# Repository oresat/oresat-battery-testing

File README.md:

# oresat-battery-testing

Battery testing software and circuitry for testing cells and batteries to fly on the ISS

General Project Documentation aimed at newcomers:
https://docs.google.com/document/d/1XBeL89PfLqN40TnOpgzCtq_2dRlRgkeDnu8u4CYXgOA/edit

V1.0 of the PCB layout:

### Software
### Setup
- Clone oresat-battery-testing.
- Install dependencies: `$ sudo apt install libusb-1.0-0-dev pkg-config python3-dev`
- Install pyusb: "pip install pyusb" or if that doesn't work, use "pip install pyusb --break-system-packages"
- Build Python extension for libb6: `$ make -C libraries`

### More Dependencies
To get u6 to work (import u6) you must install the labjack-ljm python library which is different from the labjack-ljm package

sudo pip install labjack-ljm --break-system-packages 
The above line installed labjack-ljm

You need to install Exodriver in order for u6 to work

git clone https://github.com/labjack/exodriver.git
cd exodriver
sudo ./install.sh

You will also need LabJackPython:
sudo pip install LabJackPython --break-system-packages

### Udev Setup
Copy the .rules files (from the Battery Tester folder) into the folder on your computer which contains rules files for udev.

For example on an Ubuntu system: /etc/udev/rules.d

This will allow you to run [filename].py without requiring sudo.

Note that you will have to find the correct devpaths again if you use your own device, then modify 99-b6mini.rules accordingly.

Choose a USB port on your computer to plug the battery board into and do not change it.

### Run
cd battery_tester
python battery_test_jig.py
or better yet: python testing_bay.py

If you get an import error about libb6:
...run the Makefile in battery_tester/libb6 to make an object file.

### Battery Cells
In each bank are four battery slots. The battery slot on each bank that is closest to the LabJack is slot D, then up from there is C, B, and A. Each battery slot corresponds to the charger of the same designation. If Battery A (on whichever battery bank currently selected) is not charging, something may be wrong with Charger A, for instance.

### Battery_Tester Design
__chargers_backend.py__
In the battery chargers section, does not deal with labjack at all.
Jobs:
- A) Hold the data required for charging batteries: ChargeProfile, Charger Serial Paths
- B) Hold the functions required for charging batteries: start_charging(), stop_charging(), define_charger_serial_paths()

__labjack_backend.py__
In the labjack battery data-getting section, does not interact with chargers at all.
Jobs:
- A) Hold data required for labjack commands: PINS,
	- i. Have notes about each of the functions (or at least a mention) of the functions we're using such as getAIN()
- B) Hold dataclass for collecting temperature and voltage data: class BankData
- C) Hold calculation/conversion functions for getting temps and volts: get_actual_temp(), get_data()
- D) A general STOP() function for the labjack

__scribe_backend.py__
In the labjack battery data-getting section, does not interact with anything.
Jobs:
- A) Hold functions for writing to csv file, including timestamps.

__main.py__ (or something similar)
This is the general frontend that combines all parts and holds a class with functions to charge, discharge, test, etc.
- A) Select a battery bank/battery and do any or all of the following:
	- i. Charge.
	- ii. Discharge.
	- iii. Get voltage and temperature. Write to csv with timestamp.

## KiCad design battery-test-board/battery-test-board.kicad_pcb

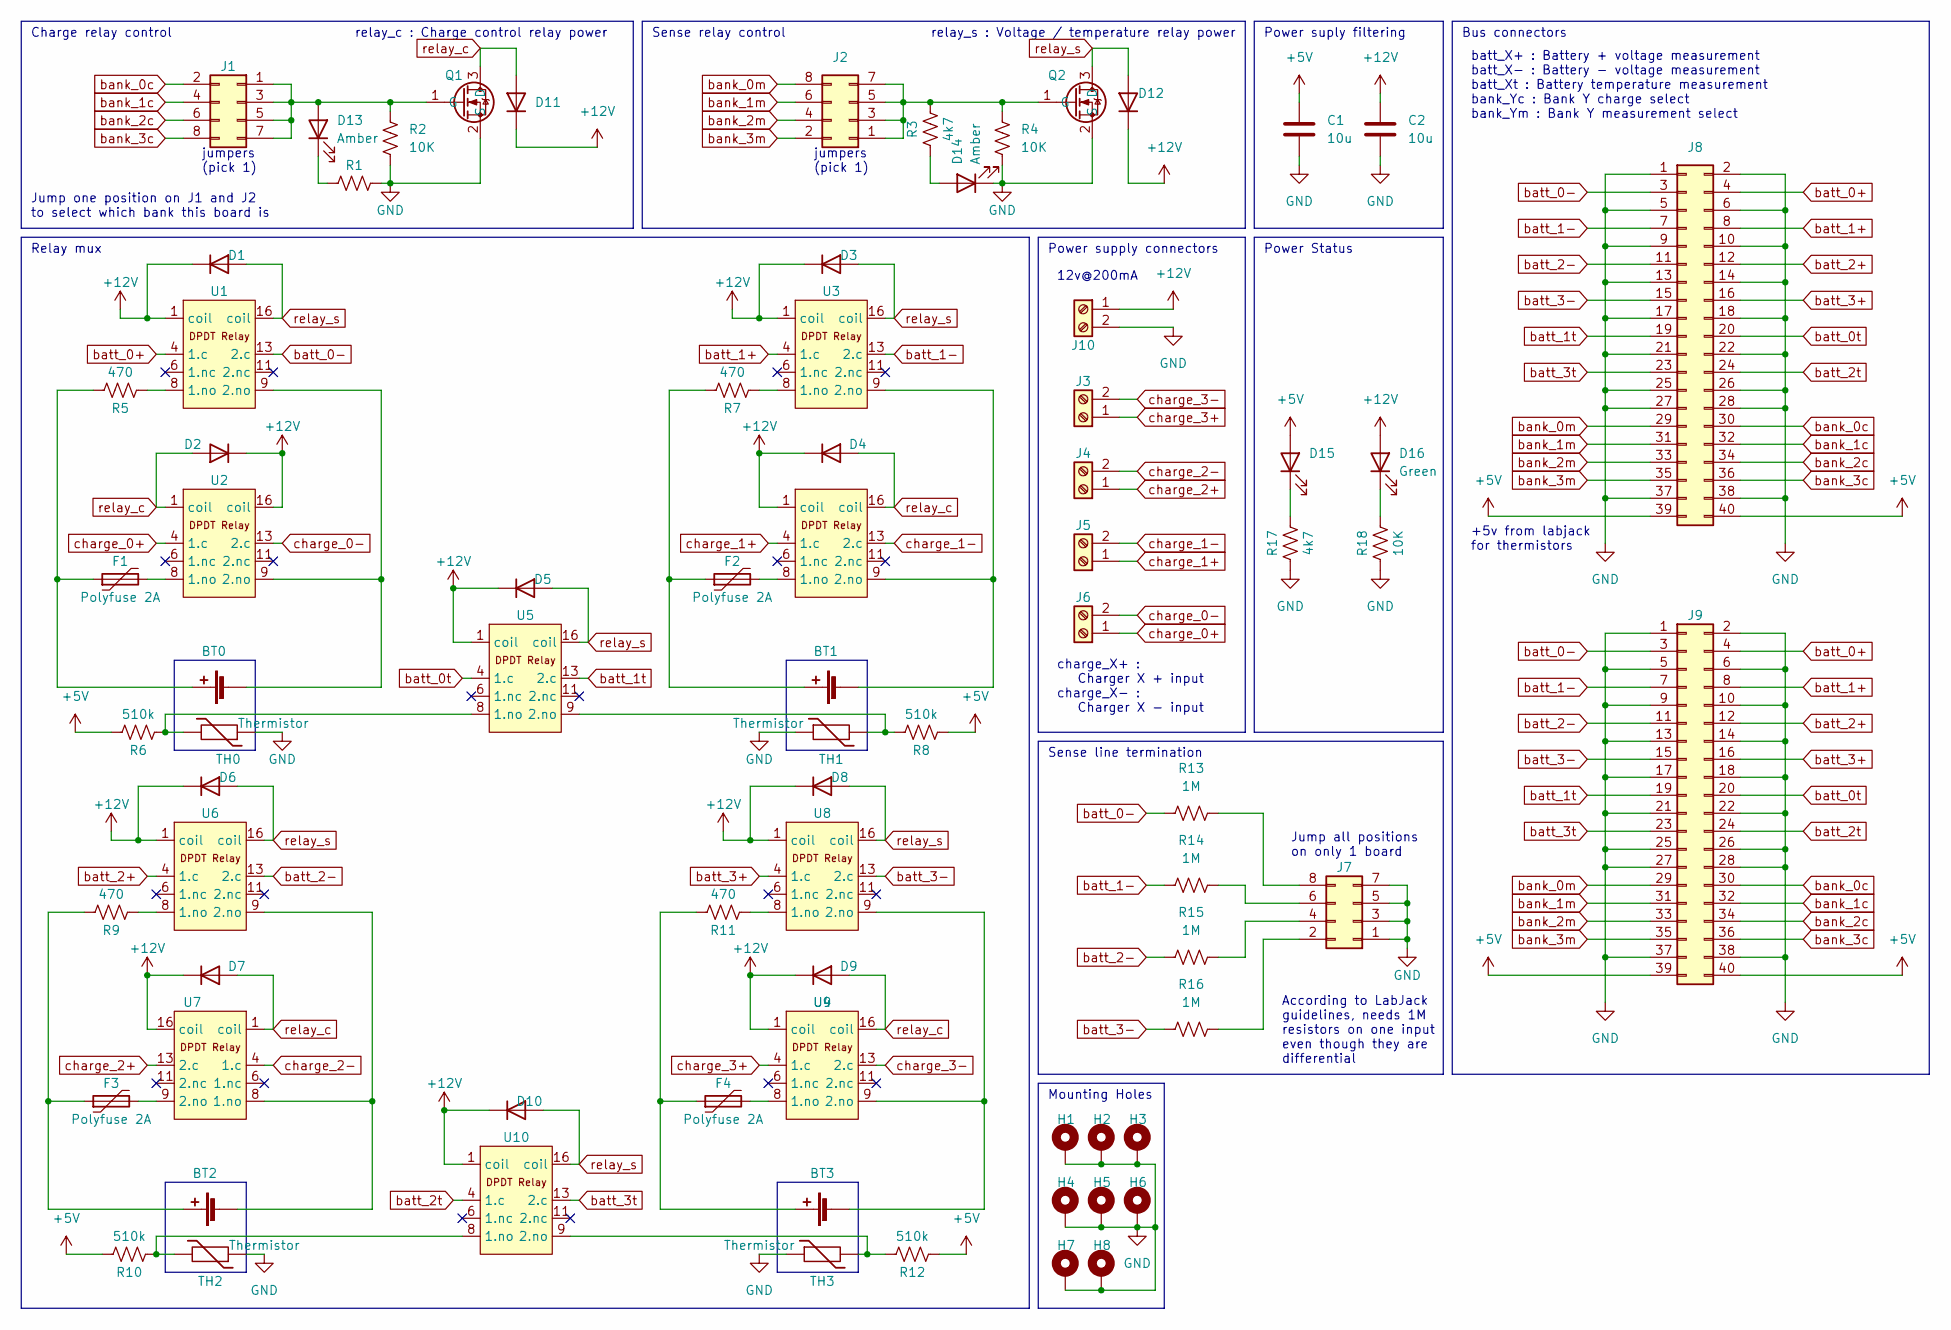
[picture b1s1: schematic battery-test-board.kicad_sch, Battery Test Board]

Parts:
BT0, BT1, BT2, BT3: battery; BatteryHolder_MPD_BH-18650-PC2; MPN BK-18650-PC2
C1, C2: 10u; C_1206_3216Metric; MPN CL31A106KAHNNNE
D1, D2, D3, D4, D5, D6, D7, D8, D9, D10, D11, D12: diode; D_0805_2012Metric; MPN NSR05T40P2T5G
D13, D14: Amber; LED_1206_3216Metric; MPN 150120AS75000
D15: MPN 150120VS75000
D16: Green; LED_1206_3216Metric; MPN 150120VS75000
F1, F2, F3, F4: Polyfuse 2A; Fuse_2920_7451Metric; MPN 2920L100PR
H1, H2, H3, H4, H5, H6, H7, H8: MountingHole_Pad; MountingHole_3.2mm_M3_Pad_Via
J1, J2, J7: Conn_02x04_Odd_Even; PinSocket_2x04_P2.54mm_Vertical; MPN PR20204VBDN
J3, J4, J5, J6, J10: Screw_Terminal_01x02; TerminalBlock_Altech_AK300-2_P5.00mm; MPN EBAA-02-C
J8, J9: connector; IDC-Header_2x20_P2.54mm_Vertical; MPN 732-5401-ND
Q1, Q2: mosfet; SOT-23; MPN PJA3412-AU_R1_000A1
R1: MPN RMCF1206FT4K70
R2, R4, R18: 10K; R_1206_3216Metric; MPN RMCF1206FT10K0
R3, R17: 4k7; R_1206_3216Metric; MPN RMCF1206FT4K70
R5, R7, R9, R11: 470; R_1206_3216Metric; MPN RMCF1206FT470R
R6, R8, R10, R12: 510k; R_1206_3216Metric; MPN RMCF1206FT510K
R13, R14, R15, R16: 1M; R_1206_3216Metric; MPN RMCF1206FT1M00
TH0, TH1, TH2, TH3: Thermistor; thermister-solderin; MPN NXFT15XH103FA1B025
U1, U2, U3, U4, U5, U6, U7, U8, U9, U10: relay; relay-dpdt-.3in; MPN J104D2C12VDC.15S‎

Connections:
+5V: C1.1, D15.2 (A), J8.39, J8.40, J9.39, J9.40, R6.1, R8.2, R10.1, R12.2
+12V: C2.1, D1.1 (K), D2.1 (K), D3.1 (K), D4.1 (K), D5.1 (K), D6.1 (K), D7.1 (K), D8.1 (K), D9.1 (K), D10.1 (K), D11.1 (K), D12.1 (K), D16.2 (A), J10.1, U1.1 (coil), U2.16 (coil), U3.1 (coil), U4.1 (coil), U5.1 (coil), U6.1 (coil), U7.16 (coil), U8.1 (coil), U9.1 (coil), U10.1 (coil)
GND: C1.2, C2.2, D14.1 (K), H1.1, H2.1, H3.1, H4.1, H5.1, H6.1, H7.1, H8.1, J7.1, J7.3, J7.5, J7.7, J8.1, J8.2, J8.5, J8.6, J8.9, J8.10, J8.13, J8.14, J8.17, J8.18, J8.21, J8.22, J8.25, J8.26, J8.27, J8.28, J8.37, J8.38, J9.1, J9.2, J9.5, J9.6, J9.9, J9.10, J9.13, J9.14, J9.17, J9.18, J9.21, J9.22, J9.25, J9.26, J9.27, J9.28, J9.37, J9.38, J10.2, Q1.2 (S), Q2.2 (S), R1.1, R2.2, R4.2, R17.2, R18.2, TH0.1, TH1.1, TH2.1, TH3.1
unnamed: BT0.1 (+), F1.1, R5.1
unnamed: BT0.2 (-), U1.9 (2.no), U2.9 (2.no)
unnamed: BT1.1 (+), F2.1, R7.1
unnamed: BT1.2 (-), U3.9 (2.no), U4.9 (2.no)
unnamed: BT2.1 (+), F3.1, R9.1
unnamed: BT2.2 (-), U6.9 (2.no), U7.8 (1.no)
unnamed: BT3.1 (+), F4.1, R11.1
unnamed: BT3.2 (-), U8.9 (2.no), U9.9 (2.no)
unnamed: D13.1 (K), R1.2
unnamed: D13.2 (A), J1.1, J1.3, J1.5, J1.7, Q1.1 (G), R2.1
unnamed: D14.2 (A), R3.2
unnamed: D15.1 (K), R17.1
unnamed: D16.1 (K), R18.1
unnamed: F1.2, U2.8 (1.no)
unnamed: F2.2, U4.8 (1.no)
unnamed: F3.2, U7.9 (2.no)
unnamed: F4.2, U9.8 (1.no)
unnamed: J2.1, J2.3, J2.5, J2.7, Q2.1 (G), R3.1, R4.1
unnamed: J7.2, R16.1
unnamed: J7.4, R15.2
unnamed: J7.6, R14.2
unnamed: J7.8, R13.2
unnamed: R5.2, U1.8 (1.no)
unnamed: R6.2, TH0.2, U5.8 (1.no)
unnamed: R7.2, U3.8 (1.no)
unnamed: R8.1, TH1.2, U5.9 (2.no)
unnamed: R9.2, U6.8 (1.no)
unnamed: R10.2, TH2.2, U10.8 (1.no)
unnamed: R11.2, U8.8 (1.no)
unnamed: R12.1, TH3.2, U10.9 (2.no)
bank_0c: J1.2, J8.30, J9.30
bank_0m: J2.8, J8.29, J9.29
bank_1c: J1.4, J8.32, J9.32
bank_1m: J2.6, J8.31, J9.31
bank_2c: J1.6, J8.34, J9.34
bank_2m: J2.4, J8.33, J9.33
bank_3c: J1.8, J8.36, J9.36
bank_3m: J2.2, J8.35, J9.35
batt_0+: J8.4, J9.4, U1.4 (1.c)
batt_0-: J8.3, J9.3, R13.1, U1.13 (2.c)
batt_0t: J8.20, J9.20, U5.4 (1.c)
batt_1+: J8.8, J9.8, U3.4 (1.c)
batt_1-: J8.7, J9.7, R14.1, U3.13 (2.c)
batt_1t: J8.19, J9.19, U5.13 (2.c)
batt_2+: J8.12, J9.12, U6.4 (1.c)
batt_2-: J8.11, J9.11, R15.1, U6.13 (2.c)
batt_2t: J8.24, J9.24, U10.4 (1.c)
batt_3+: J8.16, J9.16, U8.4 (1.c)
batt_3-: J8.15, J9.15, R16.2, U8.13 (2.c)
batt_3t: J8.23, J9.23, U10.13 (2.c)
charge_0+: J6.1, U2.4 (1.c)
charge_0-: J6.2, U2.13 (2.c)
charge_1+: J5.1, U4.4 (1.c)
charge_1-: J5.2, U4.13 (2.c)
charge_2+: J4.1, U7.13 (2.c)
charge_2-: J4.2, U7.4 (1.c)
charge_3+: J3.1, U9.4 (1.c)
charge_3-: J3.2, U9.13 (2.c)
relay_c: D2.2 (A), D4.2 (A), D7.2 (A), D9.2 (A), D11.2 (A), Q1.3 (D), U2.1 (coil), U4.16 (coil), U7.1 (coil), U9.16 (coil)
relay_s: D1.2 (A), D3.2 (A), D5.2 (A), D6.2 (A), D8.2 (A), D10.2 (A), D12.2 (A), Q2.3 (D), U1.16 (coil), U3.16 (coil), U5.16 (coil), U6.16 (coil), U8.16 (coil), U10.16 (coil)

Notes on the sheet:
jumpers (pick 1)
Jump one position on J1 and J2 to select which bank this board is
Jump all positions on only 1 board
Mounting Holes
Sense line termination
relay_c : Charge control relay power
Power Status
Sense relay control
Power supply connectors
relay_s : Voltage / temperature relay power
12v@200mA
+5v from labjack for thermistors
Power suply filtering
charge_X+ : Charger X + input charge_X- : Charger X - input
batt_X+ : Battery + voltage measurement batt_X- : Battery - voltage measurement batt_Xt : Battery temperature measurement bank_Yc : Bank Y charge select bank_Ym : Bank Y measurement select
According to LabJack guidelines, needs 1M resistors on one input even though they are differential
Relay mux
Bus connectors
Charge relay control

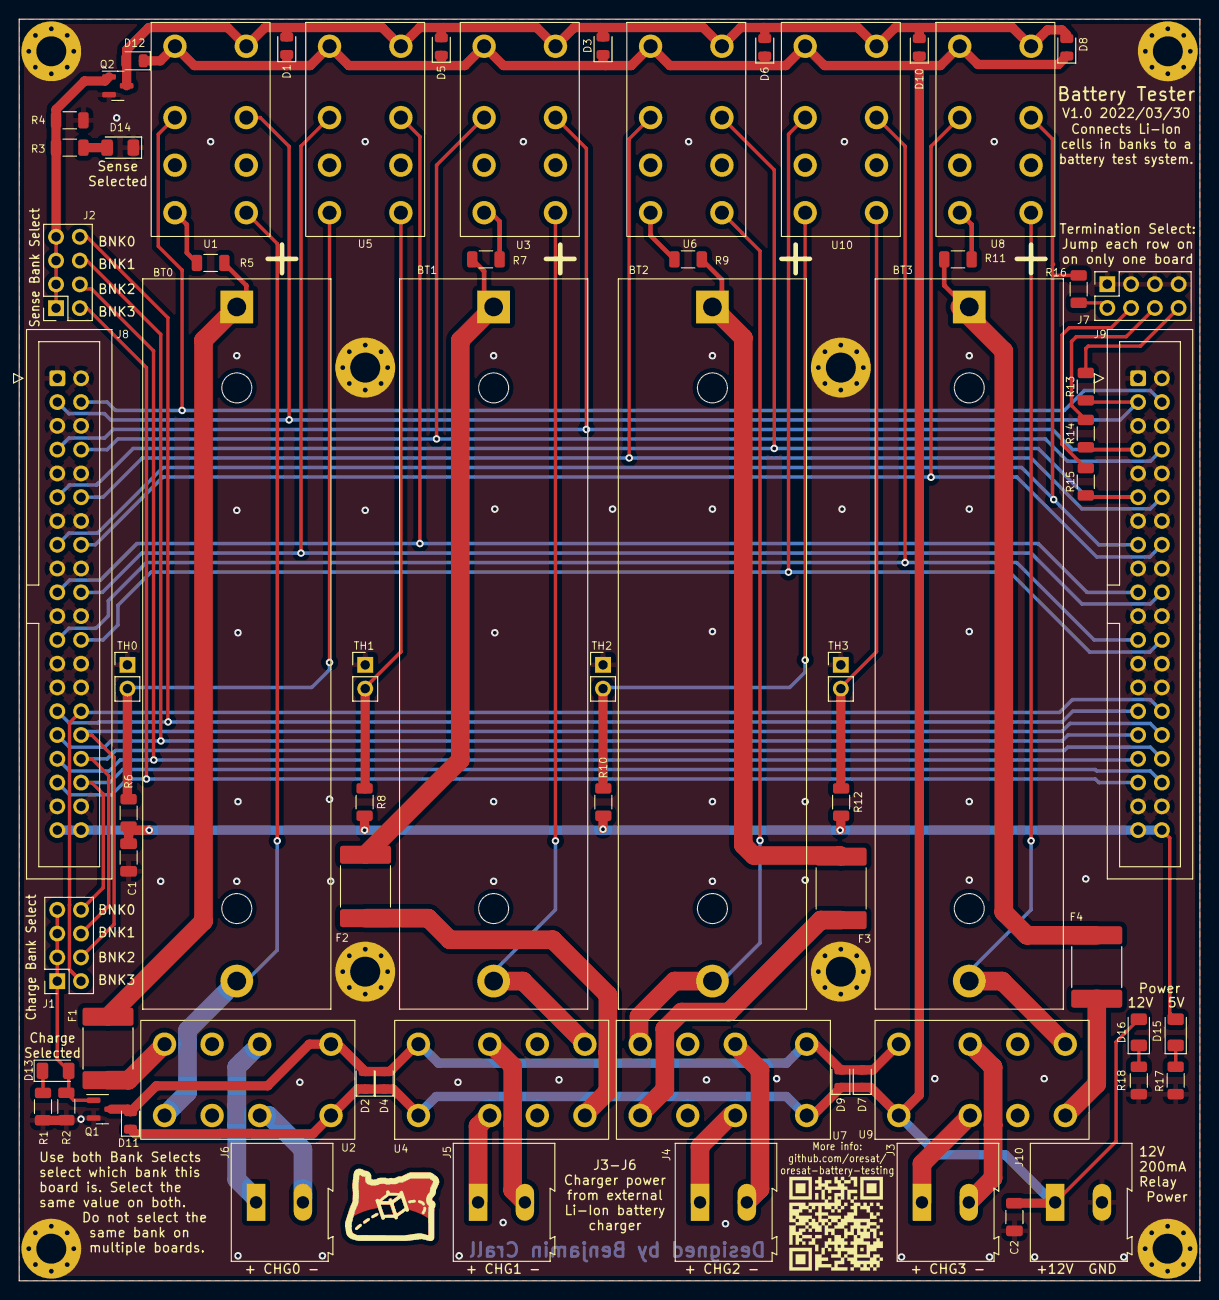
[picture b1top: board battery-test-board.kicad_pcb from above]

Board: 2 copper layers, 126.1 x 134.7 mm, 78 parts (0 on the bottom side), 63 nets.

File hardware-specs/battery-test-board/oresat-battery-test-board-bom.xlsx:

OreSat Battery Test Board v1
Qty | Parts | MFR | MPN | Description | Assembly | STOCK | DIST | DPN | DIST2 | DPN2
4 | BT0, BT1, BT2, BT3 | MPD (Memory Protection Devices) | BK-18650-PC2 | Battery Holder (Open) 18650 1 Cell PC Pin | TH |  | Digikey | BK-18650-PC2-ND
2 | C1, C2 | Samsung Electro-Mechanics | CL31A106KAHNNNE | 10 µF ±10% 25V Ceramic Capacitor X5R 1206 (3216 Metric) | SMD |  | Digikey | 1276-1075-1-ND
12 | D1, D2, D3, D4, D5, D6, D7, D8, D9, D10, D11, D12 | onsemi | NSR05T40P2T5G | Diode Schottky 40 V 500mA (DC) Surface Mount SOD-923 | SMD |  | Digikey | NSR05T40P2T5GOSCT-ND
2 | D13, D14 | Würth Elektronik | 150120AS75000 | Amber 605nm LED Indication - Discrete 2V 1206 (3216 Metric) | SMD |  | Digikey | 732-4988-1-ND
2 | D15, D16 | Würth Elektronik | 150120VS75000 | Green 570nm LED Indication - Discrete 2V 1206 (3216 Metric) | SMD |  | Digikey | 732-4993-1-ND
4 | F1, F2, F3, F4 | Littelfuse Inc. | 2920L100PR | Polymeric PTC Resettable Fuse 33V 1.1 A Ih Surface Mount 2920 (7351 Metric), Co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 | SMD |  | Digikey | F2868CT-ND
3 | J1, J2, J7 | METZ CONNECT USA Inc. | PR20204VBDN | Connector Header Through Hole 8 position 0.100" (2.54mm) | TH |  | Digikey | 1849-PR20204VBDN-ND
5 | J3, J4, J5, J6, J10 | Adam Tech | EBAA-02-C | 2 Position Wire to Board Terminal Block Horizontal with Board 0.197" (5.00mm) T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 | TH |  | Digikey | 2057-EBAA-02-C-ND
2 | J8, J9 | Würth Elektronik | 732-5401-ND | Connector Header Through Hole 40 position 0.100" (2.54mm) | TH |  | Digikey | 732-5401-ND
2 | Q1, Q2 | Panjit International Inc. | PJA3412-AU_R1_000A1 | N-Channel 20 V 4.1A (Ta) 1.25W (Ta) Surface Mount SOT-23k | SMD |  | Digikey | 3757-PJA3412-AU_R1_000A1CT-ND
3 | R1, R3, R17 | Stackpole Electronics Inc | RMCF1206FT4K70 | 4.7 kOhms ±1% 0.25W, 1/4W Chip Resistor 1206 (3216 Metric) Automotive AEC-Q200 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 | SMD |  | Digikey | RMCF1206FT4K70CT-ND
3 | R2, R4, R18 | Stackpole Electronics Inc | RMCF1206FT10K0 | 10 kOhms ±1% 0.25W, 1/4W Chip Resistor 1206 (3216 Metric) Automotive AEC-Q200 T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 | SMD |  | Digikey | RMCF1206FT10K0CT-ND
4 | R5, R7, R9, R11 | Stackpole Electronics Inc | RMCF1206FT470R | 470 Ohms ±1% 0.25W, 1/4W Chip Resistor 1206 (3216 Metric) Automotive AEC-Q200 T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 | SMD |  | Digikey | RMCF1206FT470RCT-ND
4 | R6, R8, R10, R12 | Stackpole Electronics Inc | RMCF1206FT510K | 510 kOhms ±1% 0.25W, 1/4W Chip Resistor 1206 (3216 Metric) Automotive AEC-Q200 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 | SMD |  | Digikey | RMCF1206FT510KCT-ND
4 | R13, R14, R15, R16 | Stackpole Electronics Inc | RMCF1206FT1M00 | 1 MOhms ±1% 0.25W, 1/4W Chip Resistor 1206 (3216 Metric) Automotive AEC-Q200 Th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 | SMD |  | Digikey | RMCF1206FT1M00CT-ND
4 | TH0, TH1, TH2, TH3 | Murata Electronics | NXFT15XH103FA1B025 | NTC Thermistor 10k Bead | TH |  | Digikey | 490-12817-ND
10 | U1, U2, U3, U4, U5, U6, U7, U8, U9, U10 | CIT Relay and Switch | J104D2C12VDC.15S‎ | General Purpose Relay DPDT | TH |  | Digikey | 2449-J104D2C12VDC.15S-ND

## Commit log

2022-02-25 Created V1.0 of the battery test board
2022-02-25 Added pdf schematic and PCB layout
2022-02-25 Added pretty board layout picture
2022-02-25 Added pretty picture
2022-03-29 Updated footprints and PCB
2022-03-29 Updated layout image
2022-03-31 Fixed silk screen and a few other things
2022-03-31 Finished BOM
2022-03-31 Changed silkscreen
2022-04-01 Added sticker
2022-04-01 Made stuff prettier
2022-04-02 Fixed many little issues
2022-04-03 Fixed a few issues missed last time
2022-04-03 Added BOM
2022-04-03 Updated schematic PDF
2022-04-03 Updated PCB image and PDF
2022-04-23 No changes to PCB; just changes to plotting settings.
2022-04-23 Updated .gitignore for kicad 6 and for psas temporary folders
2022-07-24 Added labjack adapter board
2022-07-25 Adjusted to OSH Park manufacturing
2022-07-25 LabJack<->test boards adapter board ready to go
2022-07-25 Added part number
2022-08-23 Added some library source code for the chargers
2022-10-01 Fixed makefile
2023-02-14 Added some stuff that apparently wasn't in Git
2023-03-16 Added csv file writer, and timestamper.
2023-03-16 Comments stuff.
2023-05-29 rework work with version other than python3.8
2023-05-29 add libb6 as a git submodule
2023-05-29 add basic software setup instructions to readme
2023-05-29 minor tab fixes to Makefile
2023-05-29 more change to Makefile
2023-05-30 python-config becomes python3-config
2023-07-02 Newest.
2023-07-02 udev rules for linux
2023-07-02 more comments
2023-07-02 current test phase
2023-07-02 list of future tasks
2023-07-02 This is branch is actually up to date.
2023-07-03 remove git submodule
2023-07-03 re-added libb6 copy
2023-07-03 added comments
2023-07-07 fixing for push request
2023-07-07 "fixed more for pull"
2023-07-09 refix for pull
2023-07-14 Uncommented code that throws error in Device.cc in libb6.
2023-07-21 added udev rule for charger USBs, added notes document for my personal use (but I'll commit it so that others can see where I'm at)
2023-08-12 testing code to get port numbers
2023-08-13 fixed args in .c file, added ignore rule for a.out
2023-08-13 name change
2023-08-14 fixing things
2023-08-14 fixing extension
2023-08-18 Working on binding!
2023-08-20 completed bindings, figuring out port number comparison
2023-08-21 added temporary test file
2023-09-01 trying to fix Device.cc (and added temp_file to test things); stoi isn't working
2023-09-02 Fixed error in custom constructor: can now adequately append port number into loc_path
2023-09-02 oh nothing really
2023-09-03 Seg faults when run, need to solve potential logic error, notes in test.py
2023-09-13 check bus number
2023-09-14 created problem, solved problem, no real change
2023-09-17 updated logic
2023-09-17 can now talk to one charger at a time, seg fault occurs when opening more than one
2023-09-17 sort of works, but has memory leaks
2023-09-17 cleaned up directory, commented out last line of destructor in Device.cc which causes seg fault, without it there will be memory leaks
2023-09-17 cleaning things up
2023-09-20 I shall clean up the repo!
2023-09-20 more cleansing
2023-09-24 .cc/.cpp to libb6 in battery_tester, dashes become underscores
2023-09-24 figuring out how to format toml file, requirements.txt might need editing too
2023-09-25 added python main
2023-10-30 added minor error check in Device.cc line 132, currently do not get seg fault while plugged in
2023-10-30 toyed around with main.cc
2023-12-04 Added new udev rule (98) for labjack to work, and now troubleshooting labjack not working.
2023-12-04 Updated documentation to add in new udev rule Problem running python module due to import issues with liblabjack and else
2023-12-04 Fixing things, but not done yet. Weird error where print statements that are deleted or commented out in Device.cc still get printed to the screen... A ghost?
2023-12-15 probably wrong syntax for __all__
2023-12-18 added note to README
2023-12-18 paper-pushing mainly, copied almost all functions from playground.py into __main__.py to enable csv writer/reader
2023-12-18 Added test directory for pytest, going through the components of labjack at current moment
2023-12-19 created new_folder to create a very simple test program
2023-12-24 fixed imports in new_folder
2023-12-25 working working working...
2023-12-25 added .ods file extension to file in hardware-specs, successfully can talk to Charger B (need to redo udev rules for all other chargers, then redo documentation for all)
2023-12-25 Charger B works, mostly!
2024-01-08 new_folder/measure.py edits: charger B can touch batteries, labjack can also read info from batteries in bank 3, about 1/8 of my board works, but it's really cool nonetheless
2024-01-08 Hehey! Have questions. Current Questions: Is the voltage and temperature data accurate (it does change depending on whether batteries are in bank versus not, but it has negative numbers which is weir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
2024-01-22 Remaking architecture
2024-01-22 more!
2024-01-22 added stop function and more
2024-01-25 Reorganized the branch. "main" is now the primary directory.
2024-02-01 need to test code for get_data function in bat-test-jig
2024-02-01 question?
2024-02-04 add pure python b6 driver
2024-02-04 add quick script to find all b6 serial devices
2024-02-05 fix bugs in libb6 when multiple u6 are used and add support for macos
2024-02-12 Trying to fix issue where sense_pin isn't setting to the correct bank
2024-02-19 Can now select sense pins on any charger. Get the correct voltage readings.
2024-02-19 All charge pins now work! Turns out they are the reverse of what was in the labjack documet (i.e. must go 7/5/3/1 for 0/1/2/3 rather than for 3/2/1/0 as was written prior
2024-02-19 Made a GUI for testing.
2024-02-19 Cleaning up bloat.
2024-02-19 Added labjack pin map pdf to folder. It will need to be re-added if it gets updated but that is unlikely.
2024-02-24 Almost done making PR changes.
2024-02-24 Test
2024-02-24 Untest
2024-02-24 Adding kicad files back.
2024-02-24 Fixed .gitignore after unfixing it.
2024-02-24 Removed temporary kicad files.
2024-02-24 Removed useless lines from udev rule 99
2024-02-26 It actually works now! Jfc
2024-02-26 Took out commented code.
2024-03-04 Added get_actual_temp function which converts thermistor reading to degrees celsius, fixed charge flag logic for GUI
2024-03-04 minor
2024-03-04 25 Battery bank 3 and 2 work with this code. There is a problem with battery bank 3 where I only get 26 two resistance readings and one is a very negative value which makes no sense. 27 Possible hard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
2024-03-10 Mispelled import
2024-03-24 Added test_BTJ.py to implement pytests for battery_test_jig
2024-03-24 Added (py)tests for BTJ's global variables.
2024-03-24 Added pytest for charger serial nums, which currently fails
2024-03-25 Added more
2024-04-01 Changed start of voltage range for lithium ions from 3100 to 3000. Added more pytests.
2024-04-01 jig_functions created
2024-04-01 Working on basic charge/discharge/measure test script.
2024-04-01 new stuffz
2024-04-08 All chargers now work for charging, so far as I can tell. Possible problem with USB numbers not matching lsusb -t values.
2024-04-14 Added README section on battery slot disambiguation.
2024-04-14 I can now select one charger at a time.
2024-04-15 Can now select individual batteries, charge em, and write the measurement data to a CSV file. Yay!
2024-04-15 Working on test_script
2024-05-26 Changed union in ChargeProfile in Device.hh to a struct, tried to bind it
2024-05-26 Might've added an effective binding of union li
2024-06-16 Minor changes.
2025-08-11 Playing with pyusb
2025-08-11 Learning pyusb for possible replacement of libb6
2025-09-15 Possible major confusion about purpose of libb6 and how to let pyusb replace it
2025-09-29 Updated README, need one to three labjack dependencies that aren't intuitive
2025-09-29 7 PyUSB is mostly to talk to chargers. LabJack functions through u6. LabJack doesn't need pyusb. 8 In other words, just use u6.function() to talk to LabJack. Write PyUSB to replace libb6 and talk 9 t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
2025-09-29 Note that BTJ in archive is wrong (made an update there rather than in the correct file pyusb_BTJ where BTJ is Battery_Test_Jig, archived files are still necessary since a lot from Device.cc and Devi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
2025-10-05 Do I need to write a checksum to the chargers? Also, next step should be to write the custom constructor in python
2025-10-26 general software design plan aadded
2025-10-26 fixing README
2025-12-22 Biggest two issues are finding USB paths (that's the final boss) and ensuring correct commands are written to the chargers
2026-01-13 Added the design document
2026-01-19 minor update to design doc
2026-01-25 Decided get_data should also append to csv file, limited cases where one would want to append without getting_data, manual addition okay in those cases
2026-02-16 volt/temp reading works and you can test this via main.py
2026-03-02 Found serial paths for this computer.
2026-03-02 message
2026-03-08 Need to convert path string to tuple
2026-03-09 confirmed that we can find the correct device
2026-03-09 The program works and connects to the correct charger, but there is no charging, suspect problem with charger write maybe its the wrong command
2026-03-09 SEE DOCUMENTATION--info on how to talk to chargers, requires python bytearray and/or struct, and checksum management
2026-03-09 quicksave, go look at the last commit message
2026-03-23 Chargers A and D seem to receive the commands but then throw an error on the hardware side, maybe something isn't plugged in right
2026-03-23 CONNECT ERROR CHECK MAIN PORT: issue on chargers A and D (though this confirms that we are successfully accessing them WHICH IS AWESOME) and then the kernel-binding issue (resource busy) on chargers 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
